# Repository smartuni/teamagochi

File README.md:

## Description

Teamagochi is a synchronized always-online pet simulator with multiplayer functionality​ by the RIOT Project SoSe24 team. 

It consists of a [physical device (Node)](./node/), [web backend](./web_backend/) and [web/mobile frontend](./web_backend/).

### [Frontend Page](https://smartuni.github.io/teamagochi/docs) [W.I.P]

### [Documentation Page](https://smartuni.github.io/teamagochi/docs)

### [Kanban Board](https://github.com/orgs/smartuni/projects/2)

## Contributing

### Cloning

Make sure to clone the repository with the `--recursive` flag to also clone the submodules.

```bash
git clone --recursive git@github.com:smartuni/teamagochi.git
```

or if you have already cloned the repository, you can run:

```bash
git submodule update --init --recursive
```

### Workflow

- Create a new branch for your feature or bugfix (`git checkout -b feature/my-feature`)
- Commit your changes (You can use VSCode or Github Desktop for an easier way to commit)
- Push to the branch (`git push origin feature/my-feature`)
- Create a Pull Request
- Ask somebody (preferably a team member) to review your code
- Wait for the reviewer to approve your PR (or ask for changes)
- Merge your PR

### Avoiding conflicts

- Make sure to keep each branch concise and focused on a single feature or bugfix
- Avoid working on multiple projects at the same time
- Merge changes from the main branch into your feature branch regularly (`git pull origin main`)
- Communicate with your team members about what you are working on

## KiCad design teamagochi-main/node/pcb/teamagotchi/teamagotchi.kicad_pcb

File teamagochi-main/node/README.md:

## Teamagochi Node

### Setup

Make sure you have cloned the repository with the `--recursive` flag to include the submodules. If you haven't, you can run `git submodule update --init --recursive` to get them.

### Development

1. Install VSCode
2. Install the C++ extension
3. Open the workspace starting from the root of the repository (Not this folder) to get the correct include paths
    1. This is also important for the linter and other settings to work correctly
4. Open a terminal at `node/code` and run `make compile-commands` to generate the compile commands file 
    1. This helps the C++ extension with intellisense

### Formatting

If you followed the development setup instructions, VSCode should automatically format the code based on the Google standards. 
Please make sure to follow the Google standards to keep the code consistent.

### Useful Commands

- `make compile-commands` - Generate the compile commands file
- `make build` - Build the project
- `make flash` - Flash the project onto the Feather
- `make term` - Open a serial terminal to the Feather
- `make clean` - Clean the build directory

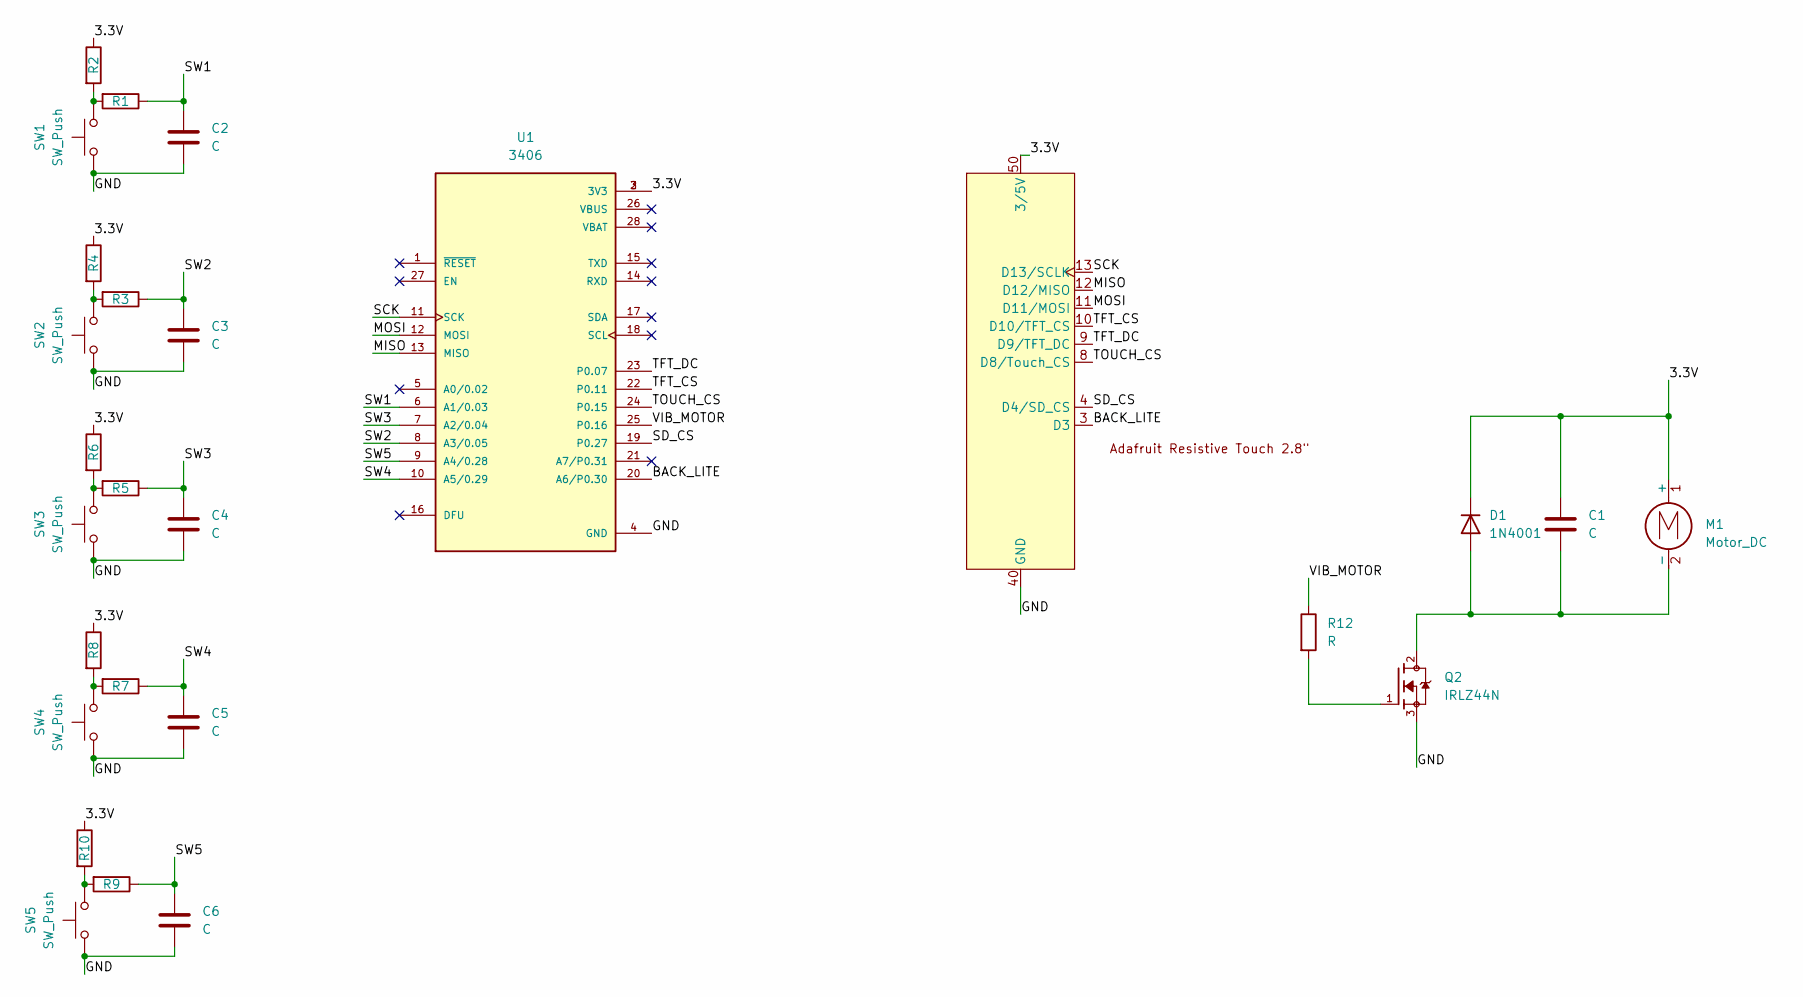
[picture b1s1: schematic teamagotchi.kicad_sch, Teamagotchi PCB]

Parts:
C1, C2, C3, C4, C5, C6: C; C_Disc_D3.0mm_W1.6mm_P2.50mm
D1: 1N4001; D_DO-41_SOD81_P10.16mm_Horizontal
M1: Motor_DC; Molex_MicroClasp_55932-0210_1x02_P2.00mm_Vertical
Q2: IRLZ44N; PARTREV 11/11/03
R1, R2, R3, R4, R5, R6, R7, R8, R9, R10, R12: R; R_Axial_DIN0204_L3.6mm_D1.6mm_P7.62mm_Horizontal
SW1, SW2, SW3, SW4, SW5: SW_Push; SW_SPST_Omron_B3F-40xx
TFT1: Display-2.8
U1: 3406; MODULE_3406; PARTREV G

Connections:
/3.3V: C1.1, D1.1 (K), M1.1 (+), R2.1, R4.1, R6.1, R8.1, R10.1, TFT1.50 (3/5V), U1.2 (3V3), U1.3 (3V3)
/BACK_LITE: TFT1.3 (D3), U1.20 (A6/P0.30)
/GND: C2.2, C3.2, C4.2, C5.2, C6.2, Q2.3, SW1.1, SW2.1, SW3.1, SW4.1, SW5.1, TFT1.40 (GND), U1.4 (GND)
/MISO: TFT1.12 (D12/MISO), U1.13 (MISO)
/MOSI: TFT1.11 (D11/MOSI), U1.12 (MOSI)
/SCK: TFT1.13 (D13/SCLK), U1.11 (SCK)
/SD_CS: TFT1.4 (D4/SD_CS), U1.19 (P0.27)
/SW1: C2.1, R1.1, U1.6 (A1/0.03)
/SW2: C3.1, R3.1, U1.8 (A3/0.05)
/SW3: C4.1, R5.1, U1.7 (A2/0.04)
/SW4: C5.1, R7.1, U1.10 (A5/0.29)
/SW5: C6.1, R9.1, U1.9 (A4/0.28)
/TFT_CS: TFT1.10 (D10/TFT_CS), U1.22 (P0.11)
/TFT_DC: TFT1.9 (D9/TFT_DC), U1.23 (P0.07)
/TOUCH_CS: TFT1.8 (D8/Touch_CS), U1.24 (P0.15)
/VIB_MOTOR: R12.1, U1.25 (P0.16)
unnamed: C1.2, D1.2 (A), M1.2 (-), Q2.2
unnamed: Q2.1, R12.2
unnamed: R1.2, R2.2, SW1.2
unnamed: R3.2, R4.2, SW2.2
unnamed: R5.2, R6.2, SW3.2
unnamed: R7.2, R8.2, SW4.2
unnamed: R9.2, R10.2, SW5.2

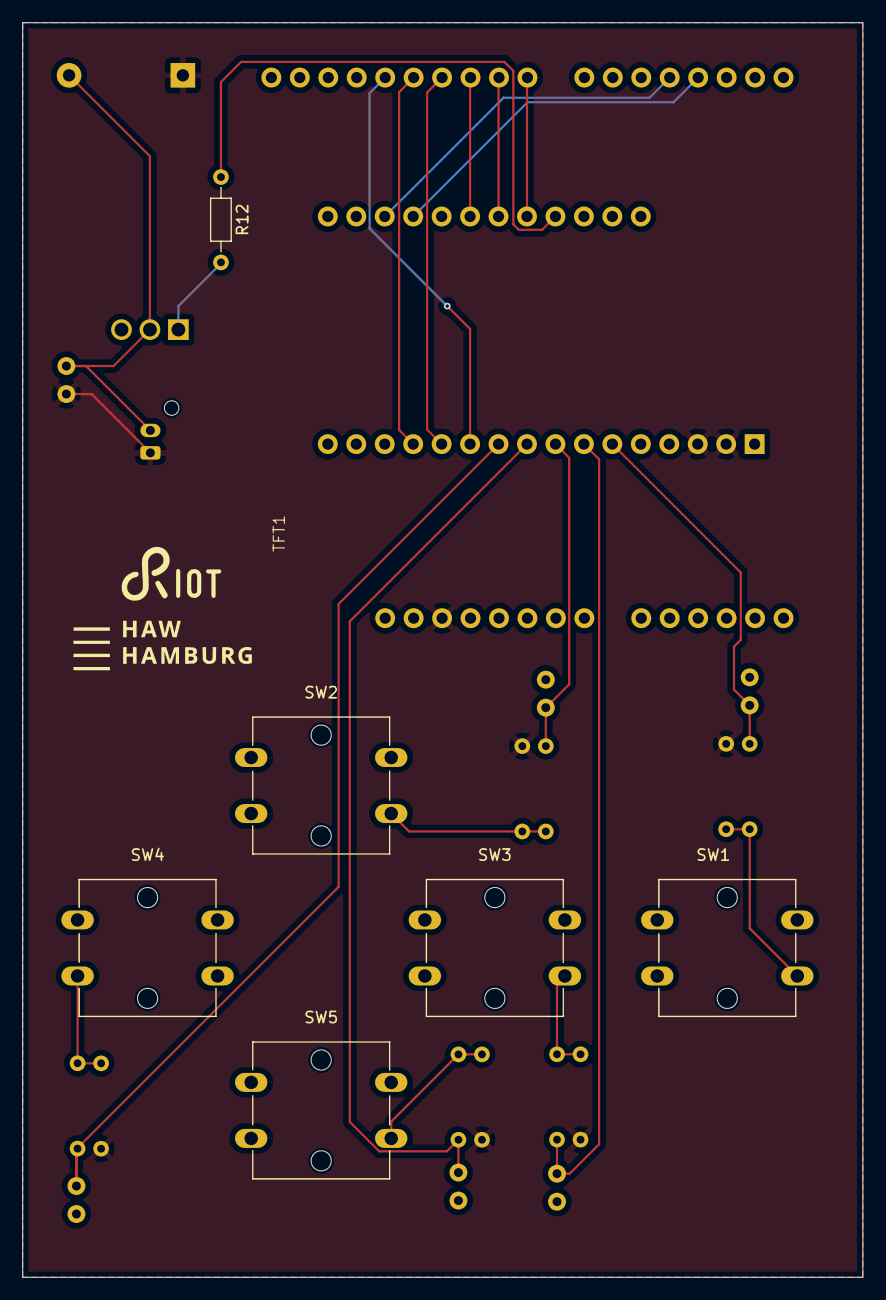
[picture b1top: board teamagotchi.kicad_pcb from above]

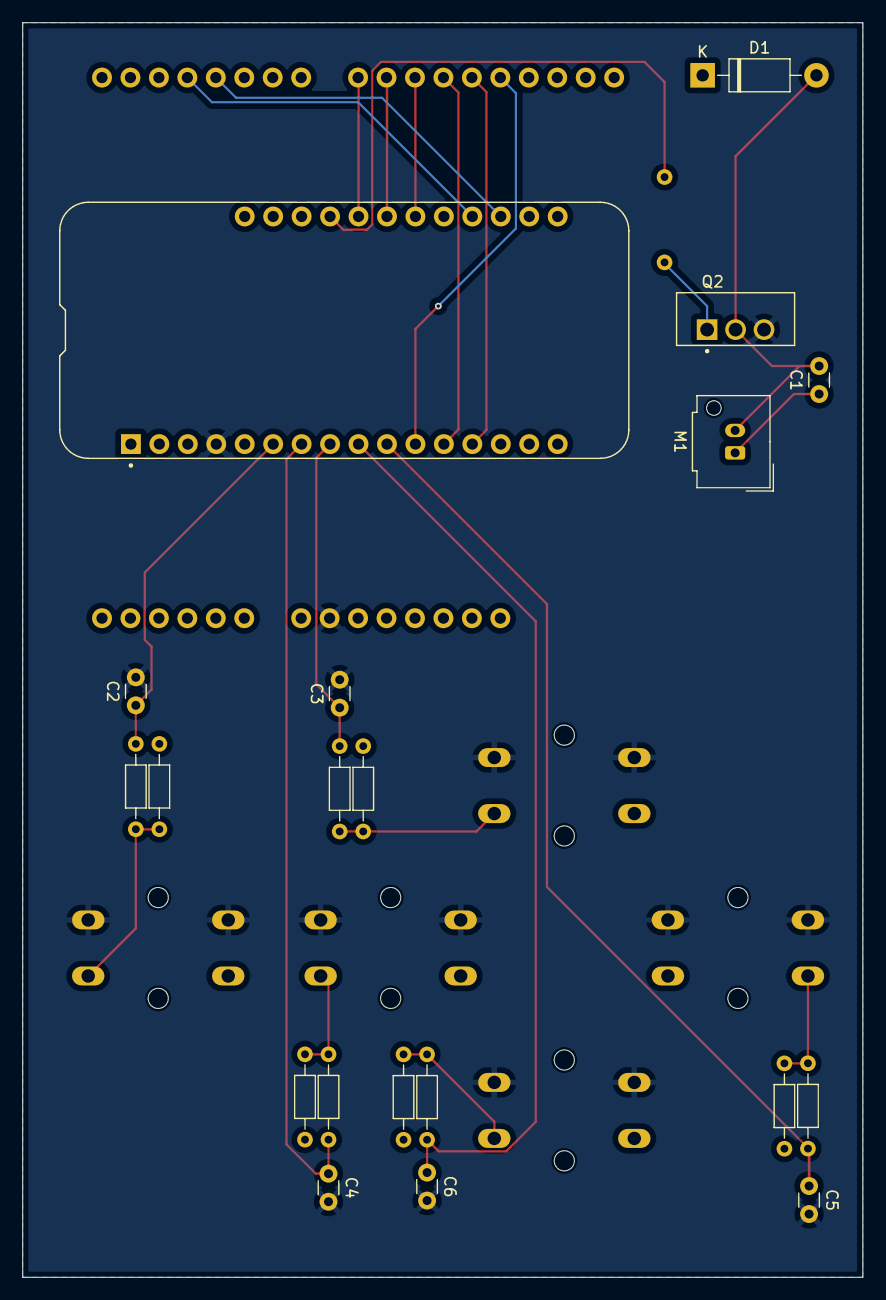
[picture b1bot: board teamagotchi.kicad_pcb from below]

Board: 2 copper layers, 75.0 x 112.0 mm, 27 parts (20 on the bottom side), 23 nets.

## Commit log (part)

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2024-05-22 changed pet object
2024-05-22 object working
2024-05-23 Removed Repos in favor of Active Record Pattern (Panache Entities)
2024-05-23 backend: move pojo generator out of maven profile
2024-05-23 backend: fix wrong maven wrapper command for windows in README.md
2024-05-27 update keycloack
2024-05-27 Added auth feature
2024-05-27 Added teamagachi favicon.
2024-05-27 Merged with main and changed folder structure: But: when starting DB says wrong passw?
2024-05-27 Created Serive-Classes for Pet and Device, worked on the DTO-Mappers
2024-05-27 Fixed Bug: DB said wrong passw.
2024-05-27 misc
2024-05-27 Method implemented: deviceExists() -> bool
2024-05-27 Fixed import on app.tsx
2024-05-27 Service expansion
2024-05-27 Fixed the auth merge
2024-05-27 created branch for navbar development
2024-05-27 Created javaDoc for Service Interfaces. + Test of constraint validation on service classes
2024-05-27 fixed merge issues, attempt 1
2024-05-27 add functions for buttons
2024-05-27 mvnw.cmd
2024-05-27 Added Navbar
2024-05-27 Add dataaccess layer
2024-05-28 changed to lab ip and encoding
2024-05-28 reduce to just test button functionality
2024-05-28 test commit
2024-05-28 keypad works
2024-05-28 deleted log
2024-05-28 deleted old code
2024-05-28 temp: buttons working, module broken
2024-05-29 fixed include issue
2024-05-29 fixed some bugs
2024-05-30 deleted io_handler
2024-05-30 backend: update quarkus to v3.11.0
2024-05-30 backend: add missing groupIds to pom.xml to fix IntelliJ bug
2024-05-30 backend: rework config in application.properties file
2024-05-30 fixed compiling issues
2024-05-31 refactoring complete, first hsm, input broken
2024-06-03 first working version
2024-06-03 added + sorted device services and pet services
2024-06-03 Dump
2024-06-03 backend: update json schemas
2024-06-03 backend: add json schema for leshan rest api endpoints (client, security) and update jsonschema2pojo config accordingly
2024-06-03 added settings page + link device funtionality
2024-06-03 profile card created
2024-06-03 backend: update leshan clients
2024-06-03 Basic Use Cases.
2024-06-03 Node. Device Model.h
2024-06-03 chore: zip pcb files to fix git invalid path error on windows
2024-06-03 Frontend navbar (#98)
2024-06-03 Use Cases are now partially tested. Created Use Case interfaces.
2024-06-03 Changes EOD: Mapper Tests and co.
2024-06-04 backend: add quarkus-rest-jackson extensions for transfer object serialization
2024-06-04 backend: add quarkus-smallrye-openapi extension to create OpenApi specification
2024-06-04 backend: minor fixes on rest clients which interferred with rest services
2024-06-04 added comments, deleted obsolute code
2024-06-04 backend: add OpenAPI spec generator and update DeviceRestService
2024-06-04 backend: update PetRestService
2024-06-04 Added dummy data and changed data structure of the entities a little.
2024-06-04 Added updated data model to docs.
2024-06-10 backend: improvements for usecase classes
2024-06-10 dummy data wasn't pushed!
2024-06-10 added progress bar
2024-06-10 dummy data + flag in application.properties
2024-06-10 Revert "chore: zip pcb files to fix git invalid path error on windows"
    This reverts commit a361bb5841107807a5dfcd1d89af5f5ffe5be76a.
2024-06-10 Remove Zone.Identifier
2024-06-10 add vibration funcs
2024-06-10 Pet Mapper Tests added and running
2024-06-10 Implemented DeviceRestService getAll, getSpecific
2024-06-10 fixed petDTOTest
2024-06-10 Added device name field in the device registration
2024-06-10 Added devide name field in device registration
2024-06-10 Updated Navbar
2024-06-10 Frontend navbar finished maybe? (#111)
2024-06-10 tests running (excluding leshan), merged with main
2024-06-10 Change background
2024-06-10 Frontend navbar final (#112)
2024-06-10 Frontend help (#113)
2024-06-10 added status bar
2024-06-10 updated Mapper-Tests
2024-06-10 added dynamic username
2024-06-10 New Icons & Background
2024-06-10 commited
2024-06-10 Auth Name (#117)
    added dynamic username for settings pase
2024-06-10 tesst vibration
2024-06-10 Added petCreate component
2024-06-11 Prototype Showcase UI
2024-06-11 chore: revert riot version downgrade by #107
2024-06-12 backend: remove redundant root .idea directory
2024-06-12 backend: update auth config
2024-06-12 backend: update keycloak exports
2024-06-13 backend: don't require Keycloak during dev and test
2024-06-13 backend: polish device service layer
2024-06-13 backend: polish device usecases
2024-06-13 backend: formatting only
2024-06-13 backend: polish pet logic and service layer
2024-06-13 backend: don't required Keycloak with dev and test profile
2024-06-13 backend: update keycloak exports, update deleteDevice(), getAllPet, AuthRestService
2024-06-13 backend: only send pet type id with dto
2024-06-13 backend: map owner and lastTimeOnDevice to PetDTO
2024-06-13 backend: fix createPet endpoint
2024-06-13 backend: add unfinished registration manager
2024-06-13 backend: improve logging for LeshanEventListener
2024-06-13 backend: finish implementation of device registration usecase
2024-06-14 backend: fix db port only on dev profile to allow parrallel execution of test and dev
2024-06-16 modified PetPage
2024-06-17 Move LwM2M object models to a directory in common ownership
2024-06-17 Minor change on resource name
2024-06-17 platform: Move LwM2M object models to a directory in common ownership (#124)
    These models are owned by the node and the backend team and this should be
    represented by the location in the repository.
2024-06-17 Model has been moved to platform
2024-06-17 platform: update objects download urls
2024-06-17 platform: add custom object specifications to leshan server and add demo client wrapper script
2024-06-17 changes to UcPetStatusImpl
2024-06-17 Updated UcPetConditions method naming
2024-06-17 platform: add keycloak redirect uri for frontend dev
2024-06-17 second Commit
2024-06-17 Updated Game-Cycle, Implemented UcPetConditionsImpl, Updated UcPetStatusImpl
2024-06-17 lwm2m/device object
2024-06-17 revert main
2024-06-17 es stürtzt nicht mehr ab
2024-06-17 timer versucht, vibriert jetzt wenn angeht
2024-06-17 Game-Cycle and Logic finished, Ballancing still needed, startet to work on Tests
2024-06-17 platform: add compose file for raspberry pi to enable ipv6
2024-06-17 Added CreatePetModal with pet creation logistics
2024-06-17 finished UcPetConditionsTests, started UcPetStatusTest 50% done
2024-06-17 LinkDevice
2024-06-17 UcPetStatusTest 80% done, UcPetInteractionsTest missing, Game-Cycle-Test missing
2024-06-17 create user if userId not found in db
2024-06-17 minor change to UcPetStatusImplTest, commit before merge with main
2024-06-17 UI for simulating device done, but pet does not get updated?
2024-06-17 Landing page.
2024-06-20 added the pet device callback
2024-06-20 backend: add quarkus docker extension and restructure properties file
2024-06-20 backend: update web_backend/README.md
2024-06-20 backend: support token auth when using Swagger UI
2024-06-20 platform: hacky preconfiguration for the leshan demo client
2024-06-20 platform: update README.md
2024-06-20 platform: fix proxy always loading the backend location include
2024-06-20 backend: dont load dummy data if database is not empty
2024-06-20 backend: add quarkus config profile to enable postres on dev (if needed for testing)
2024-06-20 backend: suppress 'Missing onFailure/onError handler in the subscriber' exception
2024-06-20 backend: fix device mapper
2024-06-20 backend: enable/disable UUID-Mock depending on Keycloak usage
2024-06-21 backend: add findDeviceByIdentifier where identifier is the LwM2M endpoint
2024-06-21 backend: allow blocking operations in sse handlers
2024-06-21 strings nearly working, but c is sometimes pain
2024-06-21 backend: write registration code to new unregistered devices
2024-06-21 dumpy1
2024-06-21 platform: make device status resource writeable
2024-06-21 platform: update device status resource description
2024-06-21 backend: temporarily remove MemoryRegistrationManagerTests
2024-06-21 Bug: Duplicate windows?
2024-06-21 Bugfix: Changes to pets were not saved in database.
2024-06-21 PetConditions code cleanup.
2024-06-21 Application Property TODO: Game Balancing konfigurierbar machen.
2024-06-21 push of string on display working
2024-06-21 Small UI changes to device sim.
2024-06-21 Gameplay change: Pet shouldn't get happy from overfeeding!
2024-06-21 TODO added.
2024-06-24 ein beliebger Code kann angezeit wird
2024-06-24 Implement long press
2024-06-24 MainView
2024-06-24 frontend: add api client demo
2024-06-24 builded
2024-06-24 Node: send_event console cmd
2024-06-24 bugs gefixt
2024-06-24 added stats view
2024-06-24 backend: revert setting PetEntity cascade types
2024-06-24 Backend fix pet mapper (#141)
2024-06-24 alles bis auf StatPage
2024-06-24 Node: Fix OK Button Event Loss
2024-06-24 add screeen off and on to fsm
2024-06-24 added documentation for the Gameplay
2024-06-24 add register code in fsm-c
2024-06-24 modified Navbar to render username
2024-06-24 OOP refactoring. TODO: testen
2024-06-24 PetEntity start values.
2024-06-24 Correction: Forgot to change xp, happy, well in UcPetInteractionsImpl.java
2024-06-24 Pet stopped being too happy. :)
2024-06-24 REACHED_MAX_STATUS event
2024-06-24 added some fsm thing, need to be tested
2024-06-24 landingpagecommit
2024-06-24 fixed strcmp compare
2024-06-28 added registerFake shellcommand + registration status is saved between on and off
2024-06-29 alles falsch
2024-06-29 scheiß timer und lv_tick.h werden nicht erkannt
2024-06-30 backend: check client endpoint name before writing to devices or handling events
2024-06-30 backend: fix CORS wildcard
2024-07-01 backend: add ssl
2024-07-01 platform: fix postgres healthcheck
2024-07-01 backend: fix production swagger url
2024-07-01 Added Uc for Pet Leaderboards and the corresponding Comparators for the pets
2024-07-01 frontend: several updates
2024-07-01 render values dynamically on pet page
2024-07-01 code working
2024-07-01 Test files.
2024-07-01 modified settings and pet modal
2024-07-01 weiter am snakeGame
2024-07-01 frontend: minor fixes
2024-07-01 frontend: add register device api
2024-07-01 Added API-Method for Leaderboard
2024-07-01 ddddd
2024-07-01 fixed pet modal
2024-07-01 Pet dying feature.
2024-07-01 Funct boolean return val --> void
2024-07-01 Buttons erkannt, game nicht zentriert
2024-07-01 modified frog image
2024-07-01 stats clean + nsake still buggy
2024-07-01 fixed pet page
2024-07-01 Test class.
2024-07-01 added event dead
2024-07-01 dunno
2024-07-01 modified pet page status bar
2024-07-01 Fixxed Anotation Problem
2024-07-01 fixed status bar
2024-07-01 Corrected Wellbeing calc.
2024-07-01 Accidental change!
2024-07-01 Interval bigger.
2024-07-01 backend: implement write pet
2024-07-01 Updated user profile Picture in Settings; Fixed Footer; Locked Pet to water type only; Shows Pets instead of devices in the settings page;
2024-07-01 Dead state noch nciht richtig
2024-07-01 snake game kind of working
2024-07-01 dont feed,play, ... while stats showing
2024-07-02 backend: add device manager, a cache for currently active devices
2024-07-02 removed navbar links
2024-07-02 backend: device manager improvements
2024-07-03 backend: hack frontend api
2024-07-03 backend: who cares
2024-07-03 backend: step by step
2024-07-03 rapsi: changes
2024-07-03 platform: fix realm import file
2024-07-04 frontend: kind of working
2024-07-04 change back to pet view
2024-07-04 game speed gets faster
2024-07-04 speed too high
2024-07-04 frontend: updates
2024-07-05 frontend: what is alive will die one day
2024-07-07 backend: implement pet object observation
2024-07-07 backend: add pet manager
2024-07-07 backend: hack game cycle interaction handling
2024-07-07 backend: chore
2024-07-07 backend: minor improvements
2024-07-07 frontend: final fruits
2024-07-08 Fix snake game
2024-07-08 Fix snake size
2024-07-08 nodes-hotfix
